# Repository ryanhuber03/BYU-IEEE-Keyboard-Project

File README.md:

# BYU-IEEE-Keyboard-Project
This is the template for both the Ergogen file and the QMK firmware that the BYU IEEE club will be using to create custom keyboards.

## Resources
 - [Ergogen guide by FlatFootFox](https://flatfootfox.com/ergogen-introduction/)
  - [Ergogen Official Website](https://ergogen.xyz/)
  - [Ergogen Auto Layout](https://pashutk.com/ergopad/)
  - [Ergogen Unofficial Website](https://ergogen.cache.works/)
  - [Ergogen Docs](https://docs.ergogen.xyz/)
 - [QMK Firmware](https://qmk.fm/)
 ## Ergogen
Ergogen is a platform that will take the dificult parts of designing a keyboard and gets you 90% of the way there with one web tool. You can use it to design a pcb, case, and face plate. One of the dificult things about it is that it recently updated to v4.0, which has breaking changes to the way it works, but the official docs hasn't been updated yet.

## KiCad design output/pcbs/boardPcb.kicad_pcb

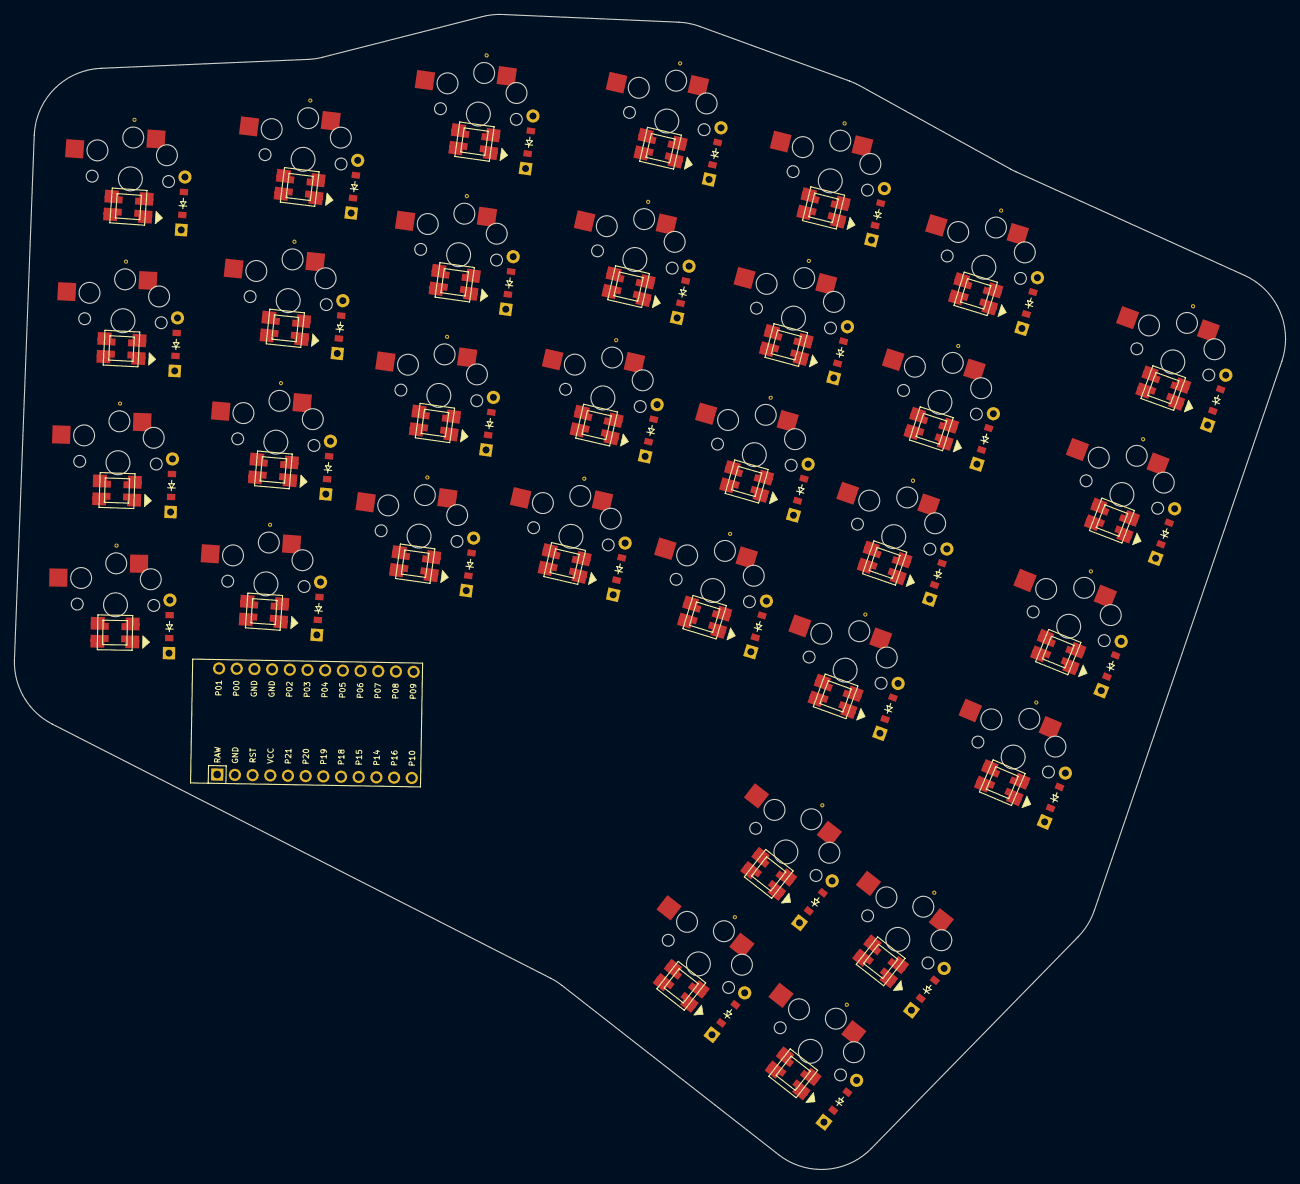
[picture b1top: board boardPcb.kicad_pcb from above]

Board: 2 copper layers, 182.5 x 165.8 mm, 129 parts (0 on the bottom side), 36 nets, no tracks yet.

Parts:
D1, D2, D3, D4, D5, D6, D7, D8, D9, D10, D11, D12, D13, D14, D15, D16, D17, D18, D19, D20, D21, D22, D23, D24, D25, D26, D27, D28, D29, D30, D31, D32: ComboDiode
LED1, LED2, LED3, LED4, LED5, LED6, LED7, LED8, LED9, LED10, LED11, LED12, LED13, LED14, LED15, LED16, LED17, LED18, LED19, LED20, LED21, LED22, LED23, LED24, LED25, LED26, LED27, LED28, LED29, LED30, LED31, LED32, LED33, LED34, LED35, LED36, LED37, LED38, LED39, LED40, LED41, LED42, LED43, LED44, LED45, LED46, LED47, LED48, LED49, LED50, LED51, LED52, LED53, LED54, LED55, LED56, LED57, LED58, LED59, LED60, LED61, LED62, LED63, LED64: WS2812B
MCU1: ProMicro
S1, S2, S3, S4, S5, S6, S7, S8, S9, S10, S11, S12, S13, S14, S15, S16, S17, S18, S19, S20, S21, S22, S23, S24, S25, S26, S27, S28, S29, S30, S31, S32: PG1350

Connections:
1_1: D29.2, S29.2
1_2: D30.2, S30.2
2_1: D31.2, S31.2
2_2: D32.2, S32.2
GND: LED1.3, LED1.33, LED2.3, LED2.33, LED3.3, LED3.33, LED4.3, LED4.33, LED5.3, LED5.33, LED6.3, LED6.33, LED7.3, LED7.33, LED8.3, LED8.33, LED9.3, LED9.33, LED10.3, LED10.33, LED11.3, LED11.33, LED12.3, LED12.33, LED13.3, LED13.33, LED14.3, LED14.33, LED15.3, LED15.33, LED16.3, LED16.33, LED17.3, LED17.33, LED18.3, LED18.33, LED19.3, LED19.33, LED20.3, LED20.33, LED21.3, LED21.33, LED22.3, LED22.33, LED23.3, LED23.33, LED24.3, LED24.33, LED25.3, LED25.33, LED26.3, LED26.33, LED27.3, LED27.33, LED28.3, LED28.33, LED29.3, LED29.33, LED30.3, LED30.33, LED31.3, LED31.33, LED32.3, LED32.33, LED33.3, LED33.33, LED34.3, LED34.33, LED35.3, LED35.33, LED36.3, LED36.33, LED37.3, LED37.33, LED38.3, LED38.33, LED39.3, LED39.33, LED40.3, LED40.33, LED41.3, LED41.33, LED42.3, LED42.33, LED43.3, LED43.33, LED44.3, LED44.33, LED45.3, LED45.33, LED46.3, LED46.33, LED47.3, LED47.33, LED48.3, LED48.33, LED49.3, LED49.33, LED50.3, LED50.33, LED51.3, LED51.33, LED52.3, LED52.33, LED53.3, LED53.33, LED54.3, LED54.33, LED55.3, LED55.33, LED56.3, LED56.33, LED57.3, LED57.33, LED58.3, LED58.33, LED59.3, LED59.33, LED60.3, LED60.33, LED61.3, LED61.33, LED62.3, LED62.33, LED63.3, LED63.33, LED64.3, LED64.33, MCU1.2, MCU1.15, MCU1.16
VCC: LED1.1, LED1.11, LED2.1, LED2.11, LED3.1, LED3.11, LED4.1, LED4.11, LED5.1, LED5.11, LED6.1, LED6.11, LED7.1, LED7.11, LED8.1, LED8.11, LED9.1, LED9.11, LED10.1, LED10.11, LED11.1, LED11.11, LED12.1, LED12.11, LED13.1, LED13.11, LED14.1, LED14.11, LED15.1, LED15.11, LED16.1, LED16.11, LED17.1, LED17.11, LED18.1, LED18.11, LED19.1, LED19.11, LED20.1, LED20.11, LED21.1, LED21.11, LED22.1, LED22.11, LED23.1, LED23.11, LED24.1, LED24.11, LED25.1, LED25.11, LED26.1, LED26.11, LED27.1, LED27.11, LED28.1, LED28.11, LED29.1, LED29.11, LED30.1, LED30.11, LED31.1, LED31.11, LED32.1, LED32.11, LED33.1, LED33.11, LED34.1, LED34.11, LED35.1, LED35.11, LED36.1, LED36.11, LED37.1, LED37.11, LED38.1, LED38.11, LED39.1, LED39.11, LED40.1, LED40.11, LED41.1, LED41.11, LED42.1, LED42.11, LED43.1, LED43.11, LED44.1, LED44.11, LED45.1, LED45.11, LED46.1, LED46.11, LED47.1, LED47.11, LED48.1, LED48.11, LED49.1, LED49.11, LED50.1, LED50.11, LED51.1, LED51.11, LED52.1, LED52.11, LED53.1, LED53.11, LED54.1, LED54.11, LED55.1, LED55.11, LED56.1, LED56.11, LED57.1, LED57.11, LED58.1, LED58.11, LED59.1, LED59.11, LED60.1, LED60.11, LED61.1, LED61.11, LED62.1, LED62.11, LED63.1, LED63.11, LED64.1, LED64.11, MCU1.4
din: LED1.4, LED1.44, LED2.4, LED2.44, LED3.4, LED3.44, LED4.4, LED4.44, LED5.4, LED5.44, LED6.4, LED6.44, LED7.4, LED7.44, LED8.4, LED8.44, LED9.4, LED9.44, LED10.4, LED10.44, LED11.4, LED11.44, LED12.4, LED12.44, LED13.4, LED13.44, LED14.4, LED14.44, LED15.4, LED15.44, LED16.4, LED16.44, LED17.4, LED17.44, LED18.4, LED18.44, LED19.4, LED19.44, LED20.4, LED20.44, LED21.4, LED21.44, LED22.4, LED22.44, LED23.4, LED23.44, LED24.4, LED24.44, LED25.4, LED25.44, LED26.4, LED26.44, LED27.4, LED27.44, LED28.4, LED28.44, LED29.4, LED29.44, LED30.4, LED30.44, LED31.4, LED31.44, LED32.4, LED32.44, LED33.4, LED33.44, LED34.4, LED34.44, LED35.4, LED35.44, LED36.4, LED36.44, LED37.4, LED37.44, LED38.4, LED38.44, LED39.4, LED39.44, LED40.4, LED40.44, LED41.4, LED41.44, LED42.4, LED42.44, LED43.4, LED43.44, LED44.4, LED44.44, LED45.4, LED45.44, LED46.4, LED46.44, LED47.4, LED47.44, LED48.4, LED48.44, LED49.4, LED49.44, LED50.4, LED50.44, LED51.4, LED51.44, LED52.4, LED52.44, LED53.4, LED53.44, LED54.4, LED54.44, LED55.4, LED55.44, LED56.4, LED56.44, LED57.4, LED57.44, LED58.4, LED58.44, LED59.4, LED59.44, LED60.4, LED60.44, LED61.4, LED61.44, LED62.4, LED62.44, LED63.4, LED63.44, LED64.4, LED64.44
dout: LED1.2, LED1.22, LED2.2, LED2.22, LED3.2, LED3.22, LED4.2, LED4.22, LED5.2, LED5.22, LED6.2, LED6.22, LED7.2, LED7.22, LED8.2, LED8.22, LED9.2, LED9.22, LED10.2, LED10.22, LED11.2, LED11.22, LED12.2, LED12.22, LED13.2, LED13.22, LED14.2, LED14.22, LED15.2, LED15.22, LED16.2, LED16.22, LED17.2, LED17.22, LED18.2, LED18.22, LED19.2, LED19.22, LED20.2, LED20.22, LED21.2, LED21.22, LED22.2, LED22.22, LED23.2, LED23.22, LED24.2, LED24.22, LED25.2, LED25.22, LED26.2, LED26.22, LED27.2, LED27.22, LED28.2, LED28.22, LED29.2, LED29.22, LED30.2, LED30.22, LED31.2, LED31.22, LED32.2, LED32.22, LED33.2, LED33.22, LED34.2, LED34.22, LED35.2, LED35.22, LED36.2, LED36.22, LED37.2, LED37.22, LED38.2, LED38.22, LED39.2, LED39.22, LED40.2, LED40.22, LED41.2, LED41.22, LED42.2, LED42.22, LED43.2, LED43.22, LED44.2, LED44.22, LED45.2, LED45.22, LED46.2, LED46.22, LED47.2, LED47.22, LED48.2, LED48.22, LED49.2, LED49.22, LED50.2, LED50.22, LED51.2, LED51.22, LED52.2, LED52.22, LED53.2, LED53.22, LED54.2, LED54.22, LED55.2, LED55.22, LED56.2, LED56.22, LED57.2, LED57.22, LED58.2, LED58.22, LED59.2, LED59.22, LED60.2, LED60.22, LED61.2, LED61.22, LED62.2, LED62.22, LED63.2, LED63.22, LED64.2, LED64.22
function_bottom: D1.2, S1.2
function_main: D2.2, S2.2
function_numbers: D4.2, S4.2
function_top: D3.2, S3.2
inner_bottom: D21.2, S21.2
inner_main: D22.2, S22.2
inner_numbers: D24.2, S24.2
inner_top: D23.2, S23.2
macro_bottom: D25.2, S25.2
macro_main: D26.2, S26.2
macro_numbers: D28.2, S28.2
macro_top: D27.2, S27.2
middle_bottom: D13.2, S13.2
middle_main: D14.2, S14.2
middle_numbers: D16.2, S16.2
middle_top: D15.2, S15.2
pinky_bottom: D5.2, S5.2
pinky_main: D6.2, S6.2
pinky_numbers: D8.2, S8.2
pinky_top: D7.2, S7.2
pointer_bottom: D17.2, S17.2
pointer_main: D18.2, S18.2
pointer_numbers: D20.2, S20.2
pointer_top: D19.2, S19.2
ring_bottom: D9.2, S9.2
ring_main: D10.2, S10.2
ring_numbers: D12.2, S12.2
ring_top: D11.2, S11.2

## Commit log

2023-10-19 Adding my yaml file
2023-10-19 Updated yaml
2023-10-26 added an outline
2023-10-26 Added a placeholder for the microcontroller: currently an arduino nano
2024-03-19 Final PCB
2024-03-19 Finished the PCB
2024-03-19 PCB done
2024-11-04 Update ergogen_V4.yaml
    Fixed author name
